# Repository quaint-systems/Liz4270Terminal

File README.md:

# Liz4270Terminal

Liz4270 is an open-source IBM 3270 CUT terminal. Its RP2350 firmware presents an IBM 3483-V to a controller over coax, drives DVI video over HDMI, and accepts a USB keyboard.

## What you need

- A Liz4270 Rev A board. The assembly order excludes the Murata 78602/8JC coax transformer (T1). Source it before ordering and fit it by hand. [Board design and bring-up](hardware/board/README.md) · [Ordering guide](hardware/board/jlc/README.md)
- A 3270 controller with a CUT coax port and a 93 Ω RG-62 cable with BNC connectors. The firmware was bench-tested on prototype hardware with oec and a Liz 4174 controller. Rev A and physical IBM 3174 bench results are still undocumented here. [oec](https://github.com/hanshuebner/oec-tcp) · [Liz 4174](https://github.com/quaint-systems/coax-tcp/tree/liz4174-v1/interface3)
- An HDMI monitor that accepts 640 × 480 at 60 Hz, a USB keyboard, and a 5 V USB-C power source. [USB keyboard map](docs/keymaps/us104.md)
- Firmware and the User’s Guide. The guide covers setup and updating over USB. [Downloads](https://github.com/quaint-systems/Liz4270Terminal/releases) · [Guide source](docs/manual/manual.typ)

For a printed enclosure, see the [printable parts and assembly instructions](hardware/case/README.md).

## Build the firmware

Install Git, CMake 3.25 or newer, Ninja, Arm GNU Toolchain 15.3.Rel1 (`arm-none-eabi`), and picotool 2.3.1. Use a Git checkout to fetch the firmware submodules.

```sh
git clone https://github.com/quaint-systems/Liz4270Terminal.git
cd Liz4270Terminal
git submodule update --init firmware/pico-sdk firmware/Pico-PIO-USB
git -C firmware/pico-sdk submodule update --init lib/tinyusb
cd firmware
cmake --preset liz4270
cmake --build --preset liz4270
```

The firmware image is `firmware/build/liz4270/liz4270.uf2`. Put the board into BOOTSEL mode and copy this file to the RP2350 USB drive. See [versioning](docs/versions.md) for how builds are identified.

## Build the user guide

Install Typst 0.15.1, Python 3.11 or newer, and a host C compiler. The manual build uses Pillow and oec to check the keyboard descriptions. Run these commands from the repository root.

```sh
git clone https://github.com/hanshuebner/oec-tcp.git ../oec-tcp
git -C ../oec-tcp checkout 3c5e812f6d2c0321e6c443dd4ed9590b7611c58a
python3 -m venv ../liz4270-docs-venv
. ../liz4270-docs-venv/bin/activate
python -m pip install -r ../oec-tcp/requirements.txt -r tools/sim/requirements.txt
PYTHONPATH=../oec-tcp python tools/manual/build.py
```

Draft PDFs for US Letter and A4 are written to `build/manual/`.

## Run the tests

See the [simulator test setup](tools/sim/README.md). To run the user guide tests as well, use the manual build environment above and run `PYTHONPATH=../oec-tcp python -m unittest discover -s tools/manual` from the repository root.

## License

- Firmware and software are licensed under [ISC](LICENSE).
- Hardware design files are licensed under [CERN-OHL-P v2](hardware/LICENSE).
- The user manual is licensed under [CC BY 4.0](docs/manual/LICENSE).
- Third-party licenses and credits are listed in [NOTICE](NOTICE).

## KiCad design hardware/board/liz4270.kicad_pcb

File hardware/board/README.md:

# Liz4270 board, revision A

The revision A board combines an RP2350B, a 3270 coax interface, DVI output, USB keyboard host, and audio.

## The schematic is generated

`liz4270.kicad_sch` and its six sheets are written by `tools/board/build_schematic.py` from `tools/board/sheet_*.py`.
**Don't edit them in KiCad**: change the sheet modules and rebuild, or the next build overwrites the edit, and
`tools/board/test_board.py` fails while the two disagree.

A sheet lists each part with its nets, as labels on short stubs, or draws a circuit with wires: `Sheet.drawing()` in
`tools/board/schematic.py`. Every sheet is drawn, with its decoupling banks and the like still listed.

```bash
python3 tools/board/build_schematic.py
python3 -m unittest discover -s tools/board -p 'test_*.py'
```

The tests need KiCad 10 (`kicad-cli`). They check the netlist against the board pin map and topology, every
supply pin's rail, which parts are fitted, every part's LCSC number, and ERC.

## Sheets

| Sheet | What |
| --- | --- |
| MCU | RP2350B on the Fruit Jam's pin map; core regulator and crystal as Raspberry Pi's minimal design; flash; BOOTSEL and RESET; SWD; the bench header; drawn as a circuit, with BOOTSEL, SWD and the bench header beside it and the decoupling listed |
| Coax | the Liz 4174's port 1 (interface3 port 0), with TX_ACTIVE's pull-down and the unused channels held; drawn as a circuit |
| Video | HSTX DVI through 220 R; TPD13S523; DDC level shifter; hot-plug to GPIO7; drawn as a circuit, with the TPD13S523's clamps by label |
| USB host | AP2171W port switch; CH334F hub; stacked dual USB-A with ESD on each port; drawn as a circuit |
| Audio | TLV320DAC3100 and its 1.8 V; speaker connector; drawn as circuits, the decoupling listed |
| Power | USB-C input and protection, 3.3 V LDO and power LED, drawn as a circuit; test points and mounting holes, bare copper that JLC's order leaves out |

## The board is generated

`liz4270.kicad_pcb`, `liz4270.kicad_pro` and `liz4270.kicad_dru` are written by `tools/board/build_board.py`, from
the schematic's netlist and `tools/board/layout.py`. **Don't save the board from KiCad**: a review that does is undone
with `git checkout hardware/board/`, and `test_layout.py` fails while the files and the generator disagree.
`build_board.py --check` builds it in a scratch directory and lists what differs.

- **The layout is Python.** `layout.py` draws the outline and runs one `layout_<block>.py` per block, in order: edge,
  MCU (with `regulator.py`, Raspberry Pi's minimal design moved onto U1), coax, video, USB host, power, audio, then
  the escapes and the planes. Each block places its parts and may add scripted copper, by pad name (`'U1.63'`) or by
  point. `pcb_build.py` runs it in KiCad's own Python (3.9, the one with `pcbnew`).
- **Coordinates** are board millimetres from the outline's top-left corner, x to the right, y down; angles turn
  counter-clockwise, as KiCad shows them. The board sits at (20, 20) on KiCad's page with the grid and drill origins
  there, so the GUI reads the same numbers as the code.
- **The floorplan,** 100 x 80 mm, four layers (In1 ground, In2 +3V3). The connector edge is the bottom, y = 80: the
  BNC (J3, x 10), USB-C (J6, x 30), the USB-A pair (J5, x 49.5), HDMI (J4, x 71), BOOTSEL behind its pinhole (SW1,
  x 85) and RESET in the corner (SW2, x 94.6).

  | Block | Where |
  | --- | --- |
  | MCU | U1 at (42, 32), turned 180°: its coax pins face left, HSTX right, the regulator, QSPI and USB down; Y1, J1 (SWD) and J2 (bench header) above it |
  | Coax | U3 and U4 at x 10–21, y 38; T1 at (10, 57); the line side, x 0–19.5 below y 59, with the BNC, inside a 1.5 mm band no copper crosses on any layer |
  | Video | R20–R27 right of U1; U6 at (75.5, 61) behind HDMI |
  | USB host | U8 at (57.75, 50), Y2, U7, and U9/U10 at the USB-A pair |
  | Power | U12 at (29, 52), U11, F1, D4 and FB1 behind USB-C |
  | Audio | U14 at (78, 16), U13 and J7 (speaker) in the top right |

- **Routing** is partly scripted and partly Freerouting's. The blocks script what must not move: TMDS and USB pairs
  matched in length, the crystals, the regulator, the coax drive and the line side, the power spines.
  `tools/board/autoroute.py` routes the rest with Freerouting 2.4.1 (a few minutes) and keeps its session beside the
  board: `liz4270.ses`, with `liz4270.route.json`, a fingerprint of everything the routes were made from (layout,
  net classes, rules, footprints). `build_board.py` takes the session in only while the fingerprint matches;
  otherwise it builds the board unrouted and says so, and `TestRouted.test_the_session_is_current` fails. A rerun
  reshuffles all of Freerouting's copper and can leave a pin or two unconnected, which an escape in
  `layout_escapes.py` fixes; check DRC after each.
- **The zones are saved unfilled.** KiCad's filler doesn't give the same polygons from one run to the next, so a
  filled board couldn't be checked byte for byte. DRC, the plots and the tests fill them; in the GUI, press B.

The other generators, each with `--check` where it writes committed files:

- `render_board.py`: PNG renders of layers, crops, or the 3D view, for looking at a layout.
- `make_models.py`: plain-body STEP models, through FreeCAD, for the footprints KiCad 10.0.6 has no model for.
- `make_exports.py`: `export/`, the outline DXF, the holes, fronts, inside parts and labels as JSON, and the same
  as an OpenSCAD include for the case (`hardware/case/`, #134); and its STEP and STL (made, not committed).
- `make_jlc.py`: `jlc/`, the Gerbers, BOM and placement file for JLC; `jlc/README.md` gives the order's options.

## Not fitted on revision A

R3 (QSPI_SS pull-up, only for another flash), U5 and C26 (coax ESD, bring-up step 7 decides), C61 (100 n on RUN, for a
board that resets by itself), J2 (bench header). None of them is on JLC's order, and neither is T1, fitted by hand
on spin 1 (`jlc/README.md`).

## Bring-up notes

- About 50 µF sits on +5V with no inrush limit, as on the Fruit Jam.
- Scope +5V while plugging in a short USB-C cable. SPKVDD and the TPD13S523 are rated only to 6.0 V, and the SMAJ5.0A
  starts clamping at 6.4 V. If +5V overshoots, add damped bulk.
- When GPIO11 goes high, the AP2171 charges about 210 µF at its current limit for about 1 ms. Check that the console
  doesn't drop.
- T1 is fitted by hand: a J-lead on a 2.54 mm pitch, line pins (1, 6) toward the BNC.

## License

CERN-OHL-P v2 (`hardware/LICENSE`, the text from
https://gitlab.com/ohwr/project/cernohl/-/wikis/uploads/3eff4154d05e7a0459f3ddbf0674cae4/cern_ohl_p_v2.txt,
where https://ohwr.org/cern_ohl_p_v2.txt redirects). The coax front end is interface3's (ISC, Hans Hübner), and the
core regulator follows Raspberry Pi's RP2350 minimal design (MIT); `NOTICE` lists both.

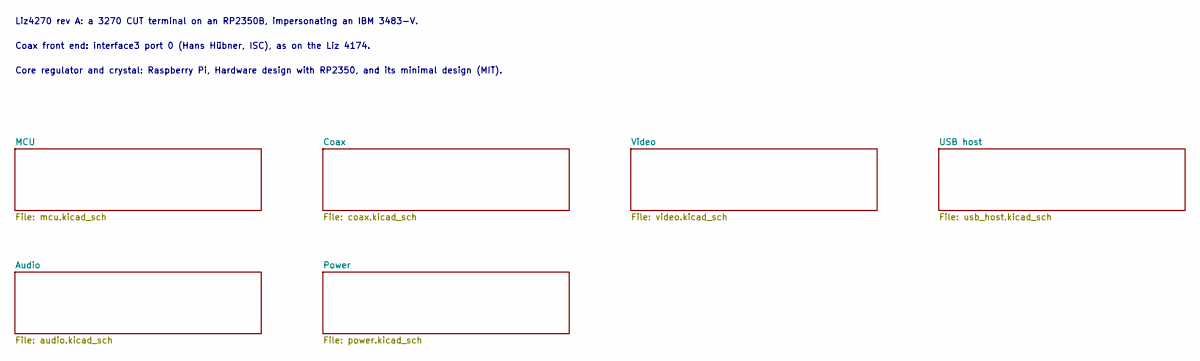
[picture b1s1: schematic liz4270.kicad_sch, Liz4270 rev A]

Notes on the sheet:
Liz4270 rev A: a 3270 CUT terminal on an RP2350B, impersonating an IBM 3483-V.
Coax front end: interface3 port 0 (Hans Hübner, ISC), as on the Liz 4174.
Core regulator and crystal: Raspberry Pi, Hardware design with RP2350, and its minimal design (MIT).

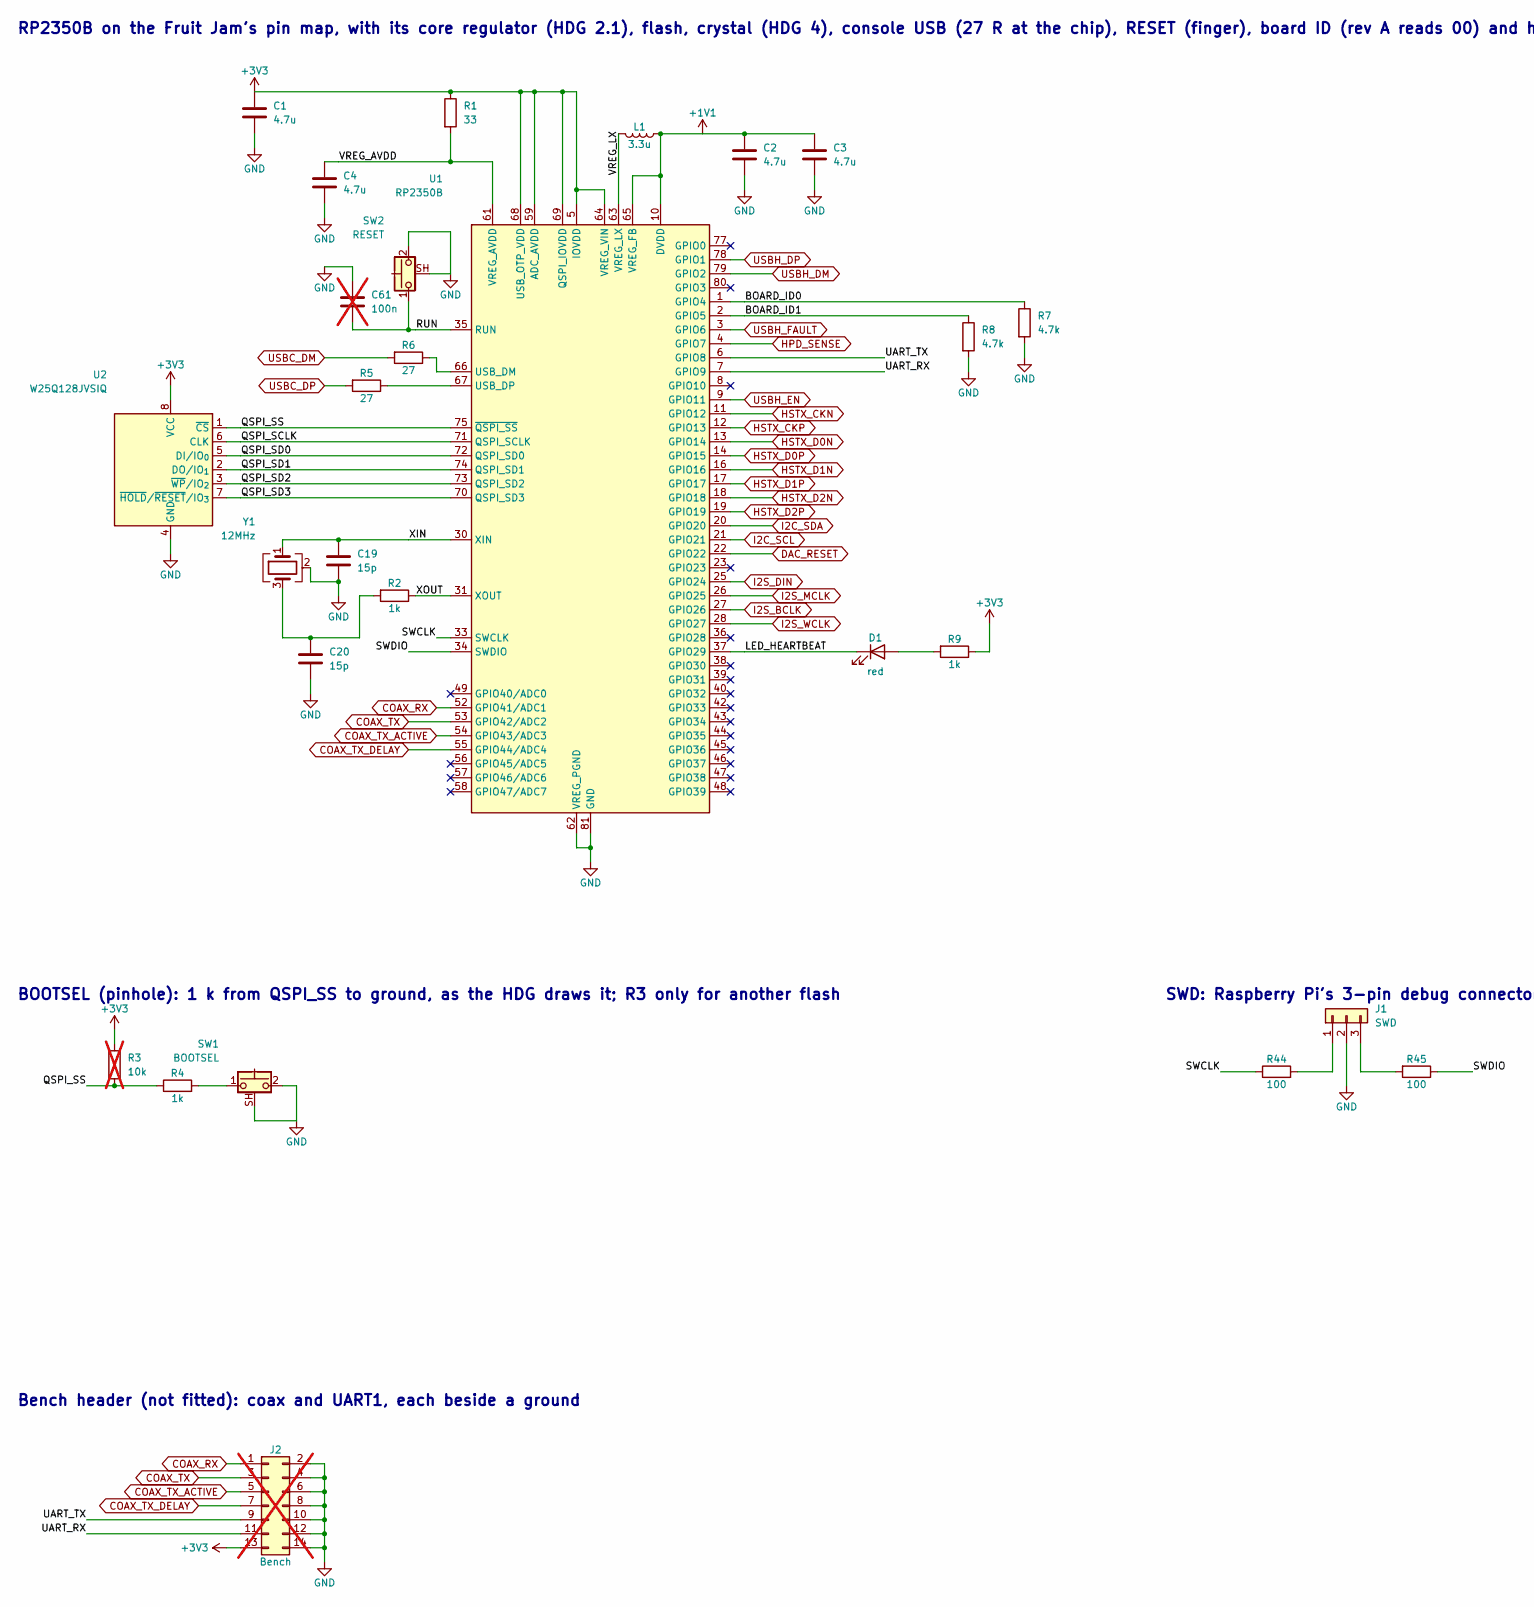
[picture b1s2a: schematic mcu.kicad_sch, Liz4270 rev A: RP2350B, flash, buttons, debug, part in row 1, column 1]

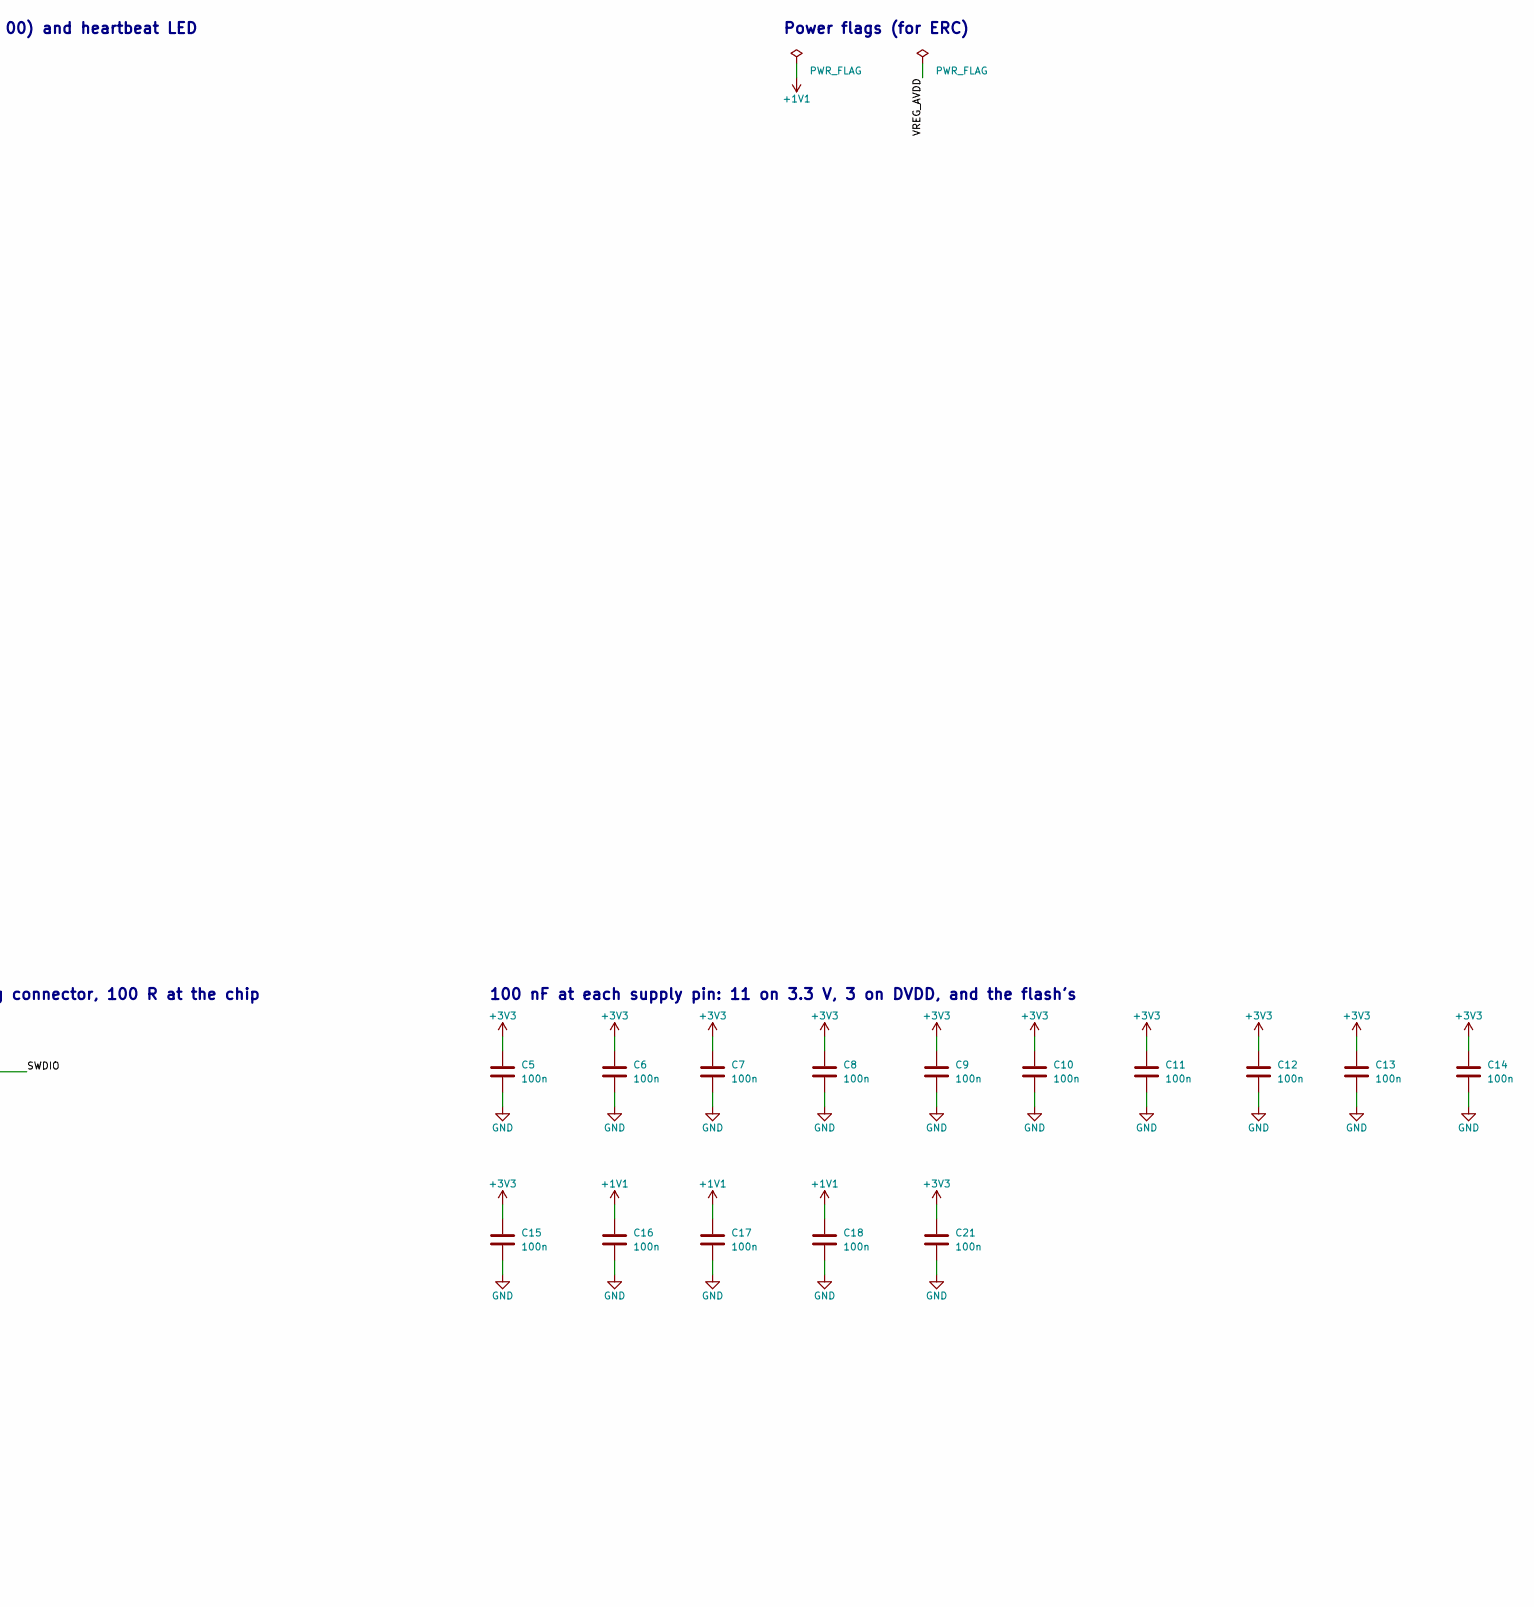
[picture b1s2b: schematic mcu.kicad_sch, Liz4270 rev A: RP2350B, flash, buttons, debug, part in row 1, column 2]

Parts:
C1, C2: 4.7u; RPi_C_1005_Wide; LCSC C23733
C3, C4: 4.7u; C_0402_1005Metric; LCSC C23733
C5, C6, C7, C8, C9, C10, C11, C12, C13, C14, C15, C16, C17, C18, C21: 100n; C_0603_1608Metric; LCSC C14663
C19, C20: 15p; C_0603_1608Metric; LCSC C1644
C61: 100n; C_0603_1608Metric; LCSC C14663; not fitted
D1: red; LED_0603_1608Metric; MPN KT-0603R; LCSC C2286
J1: SWD; JST_SH_SM03B-SRSS-TB_1x03-1MP_P1.00mm_Horizontal; MPN 1.0-3PWT; LCSC C2763613
J2: Bench; PinHeader_2x07_P2.54mm_Vertical; MPN 2.54-2*7P; LCSC C71397; not fitted
L1: 3.3u; Abracon_AOTA-B201610S3R3-101-T; MPN AOTA-B201610S3R3-101-T; LCSC C42411119
R1: 33; R_0402_1005Metric; LCSC C25105
R2, R4, R9: 1k; R_0603_1608Metric; LCSC C21190
R3: 10k; R_0603_1608Metric; LCSC C25804; not fitted
R5, R6: 27; R_0603_1608Metric; LCSC C25190
R7, R8: 4.7k; R_0603_1608Metric; LCSC C23162
R44, R45: 100; R_0603_1608Metric; LCSC C22775
SW1: BOOTSEL; SW_CK_PTS645V_Angled; MPN PTS645VK392LFS; LCSC C285519
SW2: RESET; SW_CK_PTS645V_Angled; MPN PTS645VK392LFS; LCSC C285519
U1: RP2350B; QFN-80-1EP_10x10mm_P0.4mm_EP3.4x3.4mm_ThermalVias; MPN RP2350B; LCSC C42415655
U2: W25Q128JVSIQ; SOIC-8_5.3x5.3mm_P1.27mm; MPN W25Q128JVSIQ; LCSC C97521
Y1: 12MHz; Crystal_SMD_3225-4Pin_3.2x2.5mm; MPN ABM8-272-T3; LCSC C20625731

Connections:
+1V1: C2.1, C3.1, C16.1, C17.1, C18.1, L1.1, U1.10 (DVDD), U1.32 (DVDD), U1.51 (DVDD), U1.65 (VREG_FB); also elsewhere on the board
+3V3: C1.1, C5.1, C6.1, C7.1, C8.1, C9.1, C10.1, C11.1, C12.1, C13.1, C14.1, C15.1, C21.1, J2.13, R1.1, R3.1, R9.1, U1.5 (IOVDD), U1.15 (IOVDD), U1.24 (IOVDD), U1.29 (IOVDD), U1.41 (IOVDD), U1.50 (IOVDD), U1.59 (ADC_AVDD), U1.60 (IOVDD), U1.64 (VREG_VIN), U1.68 (USB_OTP_VDD), U1.69 (QSPI_IOVDD), U1.76 (IOVDD), U2.8 (VCC); also elsewhere on the board
/MCU/BOARD_ID0: R7.1, U1.1 (GPIO4)
/MCU/BOARD_ID1: R8.1, U1.2 (GPIO5)
/MCU/LED_HEARTBEAT: D1.1 (K), U1.37 (GPIO29)
/MCU/QSPI_SCLK: U1.71 (QSPI_SCLK), U2.6 (CLK)
/MCU/QSPI_SD0: U1.72 (QSPI_SD0), U2.5 (DI/IO_{0})
/MCU/QSPI_SD1: U1.74 (QSPI_SD1), U2.2 (DO/IO_{1})
/MCU/QSPI_SD2: U1.73 (QSPI_SD2), U2.3 (~WP/IO_{2})
/MCU/QSPI_SD3: U1.70 (QSPI_SD3), U2.7 (~HOLD/~RESET/IO_{3})
/MCU/QSPI_SS: R3.2, R4.1, U1.75 (~QSPI_SS), U2.1 (~CS)
/MCU/RUN: C61.1, SW2.1, U1.35 (RUN)
/MCU/SWCLK: R44.1, U1.33 (SWCLK)
/MCU/SWDIO: R45.1, U1.34 (SWDIO)
/MCU/UART_RX: J2.11, U1.7 (GPIO9)
/MCU/UART_TX: J2.9, U1.6 (GPIO8)
/MCU/VREG_AVDD: C4.1, R1.2, U1.61 (VREG_AVDD)
/MCU/VREG_LX: L1.2, U1.63 (VREG_LX)
/MCU/XIN: C19.1, U1.30 (XIN), Y1.1
/MCU/XOUT: R2.1, U1.31 (XOUT)
COAX_RX: J2.1, U1.52 (GPIO41/ADC1); also elsewhere on the board
COAX_TX: J2.3, U1.53 (GPIO42/ADC2); also elsewhere on the board
COAX_TX_ACTIVE: J2.5, U1.54 (GPIO43/ADC3); also elsewhere on the board
COAX_TX_DELAY: J2.7, U1.55 (GPIO44/ADC4); also elsewhere on the board
DAC_RESET: U1.22 (GPIO22); also elsewhere on the board
GND: C1.2, C2.2, C3.2, C4.2, C5.2, C6.2, C7.2, C8.2, C9.2, C10.2, C11.2, C12.2, C13.2, C14.2, C15.2, C16.2, C17.2, C18.2, C19.2, C20.2, C21.2, C61.2, J1.2, J2.2, J2.4, J2.6, J2.8, J2.10, J2.12, J2.14, R7.2, R8.2, SW1.2, SW1.SH (B), SW2.2, SW2.SH (B), U1.62 (VREG_PGND), U1.81 (GND), U2.4 (GND), Y1.2 (G), Y1.4 (G); also elsewhere on the board
HPD_SENSE: U1.4 (GPIO7); also elsewhere on the board
HSTX_CKN: U1.11 (GPIO12); also elsewhere on the board
HSTX_CKP: U1.12 (GPIO13); also elsewhere on the board
HSTX_D0N: U1.13 (GPIO14); also elsewhere on the board
HSTX_D0P: U1.14 (GPIO15); also elsewhere on the board
HSTX_D1N: U1.16 (GPIO16); also elsewhere on the board
HSTX_D1P: U1.17 (GPIO17); also elsewhere on the board
HSTX_D2N: U1.18 (GPIO18); also elsewhere on the board
HSTX_D2P: U1.19 (GPIO19); also elsewhere on the board
I2C_SCL: U1.21 (GPIO21); also elsewhere on the board
I2C_SDA: U1.20 (GPIO20); also elsewhere on the board
I2S_BCLK: U1.27 (GPIO26); also elsewhere on the board
I2S_DIN: U1.25 (GPIO24); also elsewhere on the board
I2S_MCLK: U1.26 (GPIO25); also elsewhere on the board
I2S_WCLK: U1.28 (GPIO27); also elsewhere on the board
unnamed: C20.1, R2.2, Y1.3
unnamed: D1.2 (A), R9.2
unnamed: J1.1, R44.2
unnamed: J1.3, R45.2
unnamed: R4.2, SW1.1
unnamed: R6.1, U1.66 (USB_DM)
unnamed: R5.1, U1.67 (USB_DP)
USBC_DM: R6.2; also elsewhere on the board
USBC_DP: R5.2; also elsewhere on the board
USBH_DM: U1.79 (GPIO2); also elsewhere on the board
USBH_DP: U1.78 (GPIO1); also elsewhere on the board
USBH_EN: U1.9 (GPIO11); also elsewhere on the board
USBH_FAULT: U1.3 (GPIO6); also elsewhere on the board

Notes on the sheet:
RP2350B on the Fruit Jam's pin map, with its core regulator (HDG 2.1), flash, crystal (HDG 4), console USB (27 R at the chip), RESET (finger), board ID (rev A reads 00) and heartbeat LED
Power flags (for ERC)
BOOTSEL (pinhole): 1 k from QSPI_SS to ground, as the HDG draws it; R3 only for another flash
SWD: Raspberry Pi's 3-pin debug connector, 100 R at the chip
100 nF at each supply pin: 11 on 3.3 V, 3 on DVDD, and the flash's
Bench header (not fitted): coax and UART1, each beside a ground

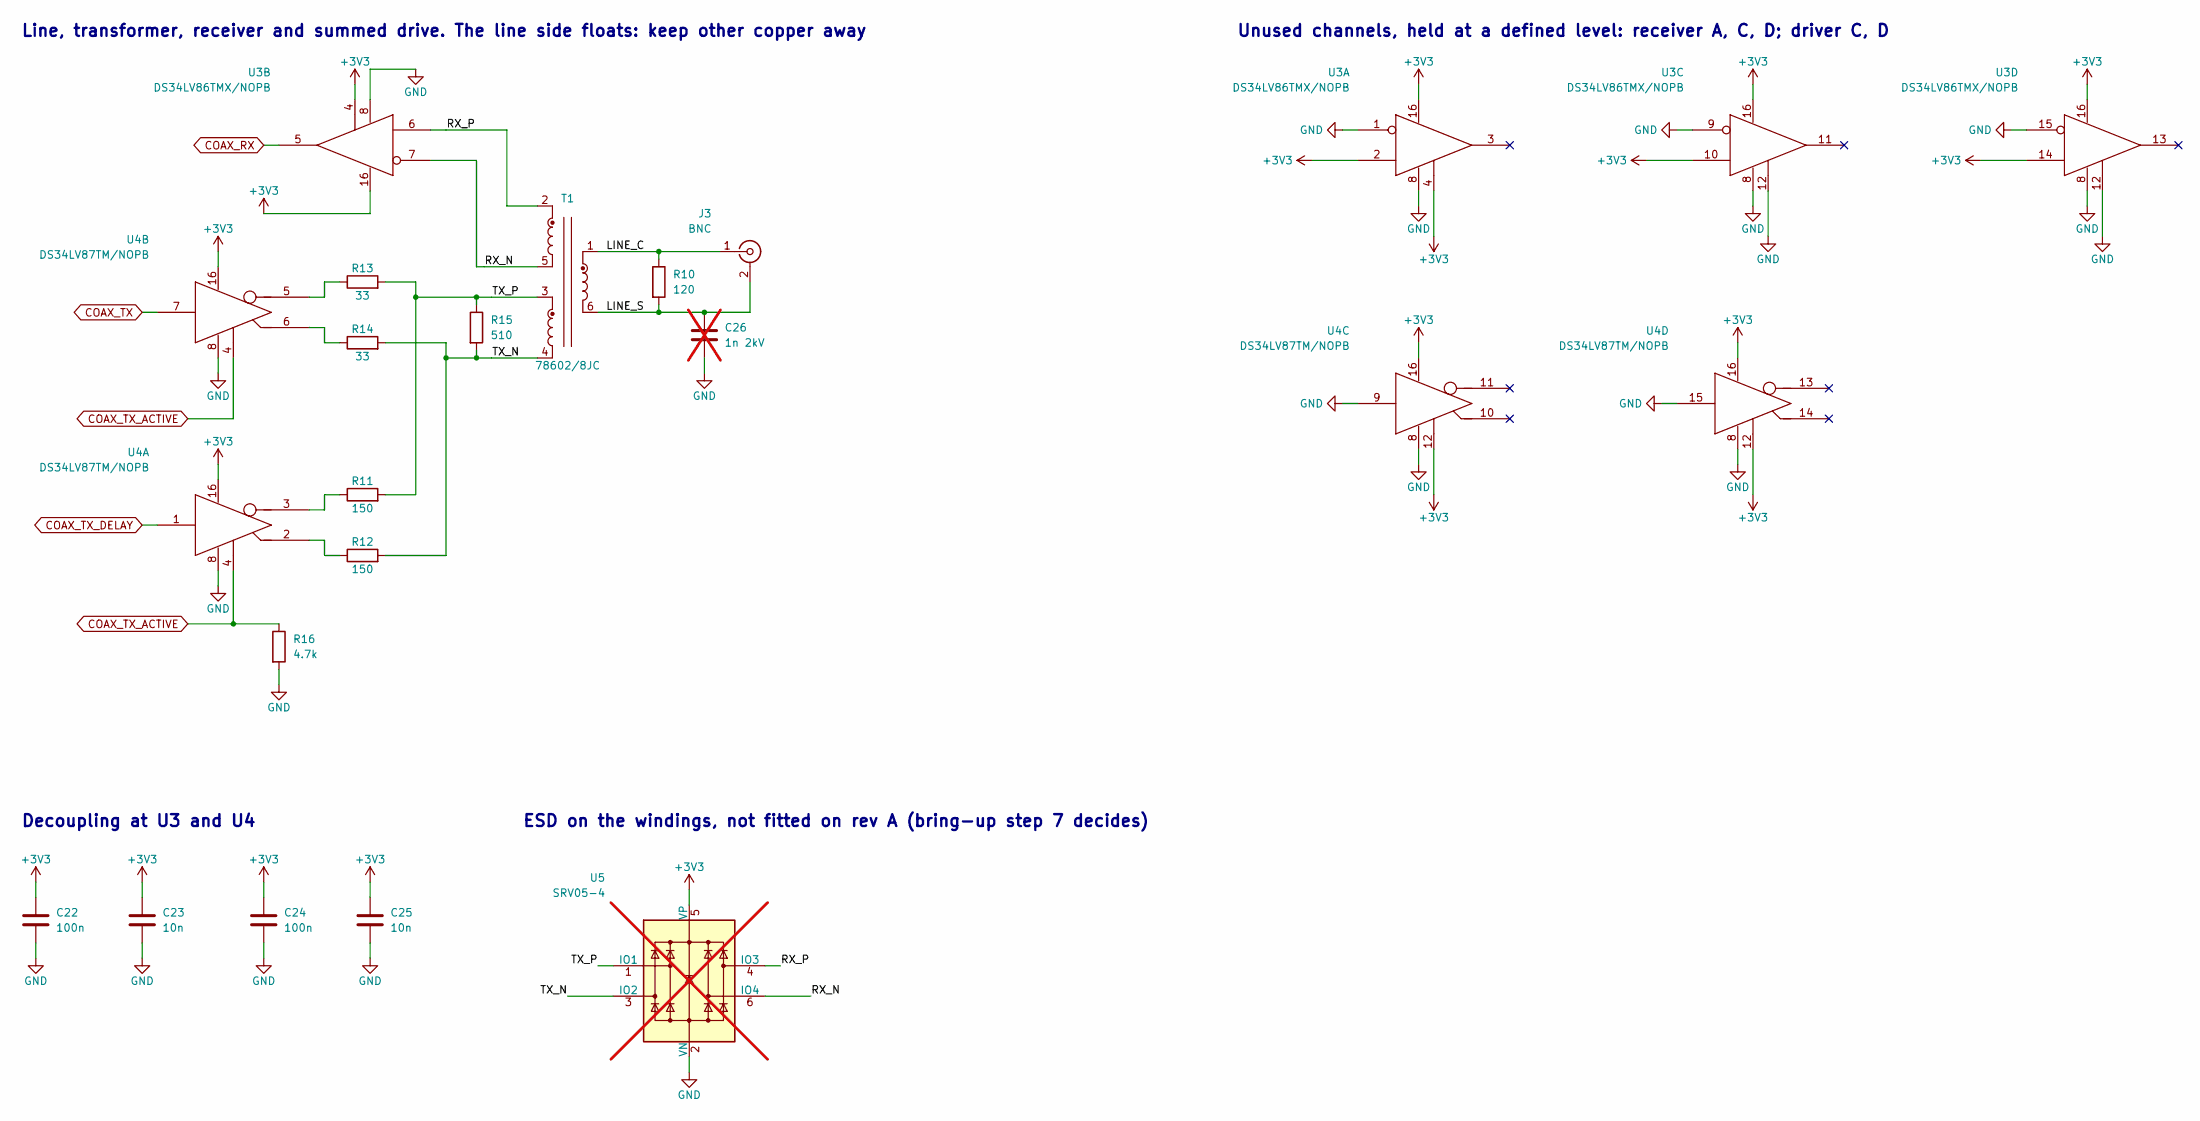
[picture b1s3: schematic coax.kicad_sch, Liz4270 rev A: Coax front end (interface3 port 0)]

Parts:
C22, C24: 100n; C_0603_1608Metric; LCSC C14663
C23, C25: 10n; C_0603_1608Metric; LCSC C57112
C26: 1n 2kV; C_1206_3216Metric; LCSC C9196; not fitted
J3: BNC; BNC_Amphenol_B6252HB-NPP3G-50_Horizontal; MPN B6252HB-NPP3G-50; LCSC C22457552
R10: 120; R_0603_1608Metric; LCSC C22787
R11, R12: 150; R_0603_1608Metric; LCSC C22808
R13, R14: 33; R_0603_1608Metric; LCSC C23140
R15: 510; R_0603_1608Metric; LCSC C23193
R16: 4.7k; R_0603_1608Metric; LCSC C23162
T1: 78602/8JC; Murata_786J; MPN 78602/8JC; LCSC C7040198
U3: DS34LV86TMX/NOPB; SOIC-16_3.9x9.9mm_P1.27mm; MPN DS34LV86TMX/NOPB; LCSC C140249
U4: DS34LV87TM/NOPB; SOIC-16_3.9x9.9mm_P1.27mm; MPN DS34LV87TM/NOPB; LCSC C1543778
U5: SRV05-4; SOT-23-6; MPN SRV05-4.TCT; LCSC C13612; not fitted

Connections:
+3V3: C22.1, C23.1, C24.1, C25.1, U3.2 (E+), U3.4 (ENABLE), U3.10 (E+), U3.14 (E+), U3.16 (VCC), U4.12 (ENABLE), U4.16 (VCC), U5.5 (VP); also elsewhere on the board
/Coax/LINE_C: J3.1 (In), R10.1, T1.1
/Coax/LINE_S: C26.1, J3.2 (Ext), R10.2, T1.6
/Coax/RX_N: T1.5, U3.7 (E-), U5.6 (IO4)
/Coax/RX_P: T1.2, U3.6 (E+), U5.4 (IO3)
/Coax/TX_N: R12.2, R14.2, R15.2, T1.4, U5.3 (IO2)
/Coax/TX_P: R11.2, R13.2, R15.1, T1.3, U5.1 (IO1)
COAX_RX: U3.5 (OUT); also elsewhere on the board
COAX_TX: U4.7 (INPUT); also elsewhere on the board
COAX_TX_ACTIVE: R16.1, U4.4 (ENABLE); also elsewhere on the board
COAX_TX_DELAY: U4.1 (INPUT); also elsewhere on the board
GND: C22.2, C23.2, C24.2, C25.2, C26.2, R16.2, U3.1 (E-), U3.8 (GND), U3.9 (E-), U3.12 (ENABLE), U3.15 (E-), U4.8 (GND), U4.9 (INPUT), U4.15 (INPUT), U5.2 (VN); also elsewhere on the board
unnamed: R12.1, U4.2 (OUT+)
unnamed: R11.1, U4.3 (OUT-)
unnamed: R14.1, U4.6 (OUT+)
unnamed: R13.1, U4.5 (OUT-)

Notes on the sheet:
Line, transformer, receiver and summed drive. The line side floats: keep other copper away
Unused channels, held at a defined level: receiver A, C, D; driver C, D
Decoupling at U3 and U4
ESD on the windings, not fitted on rev A (bring-up step 7 decides)

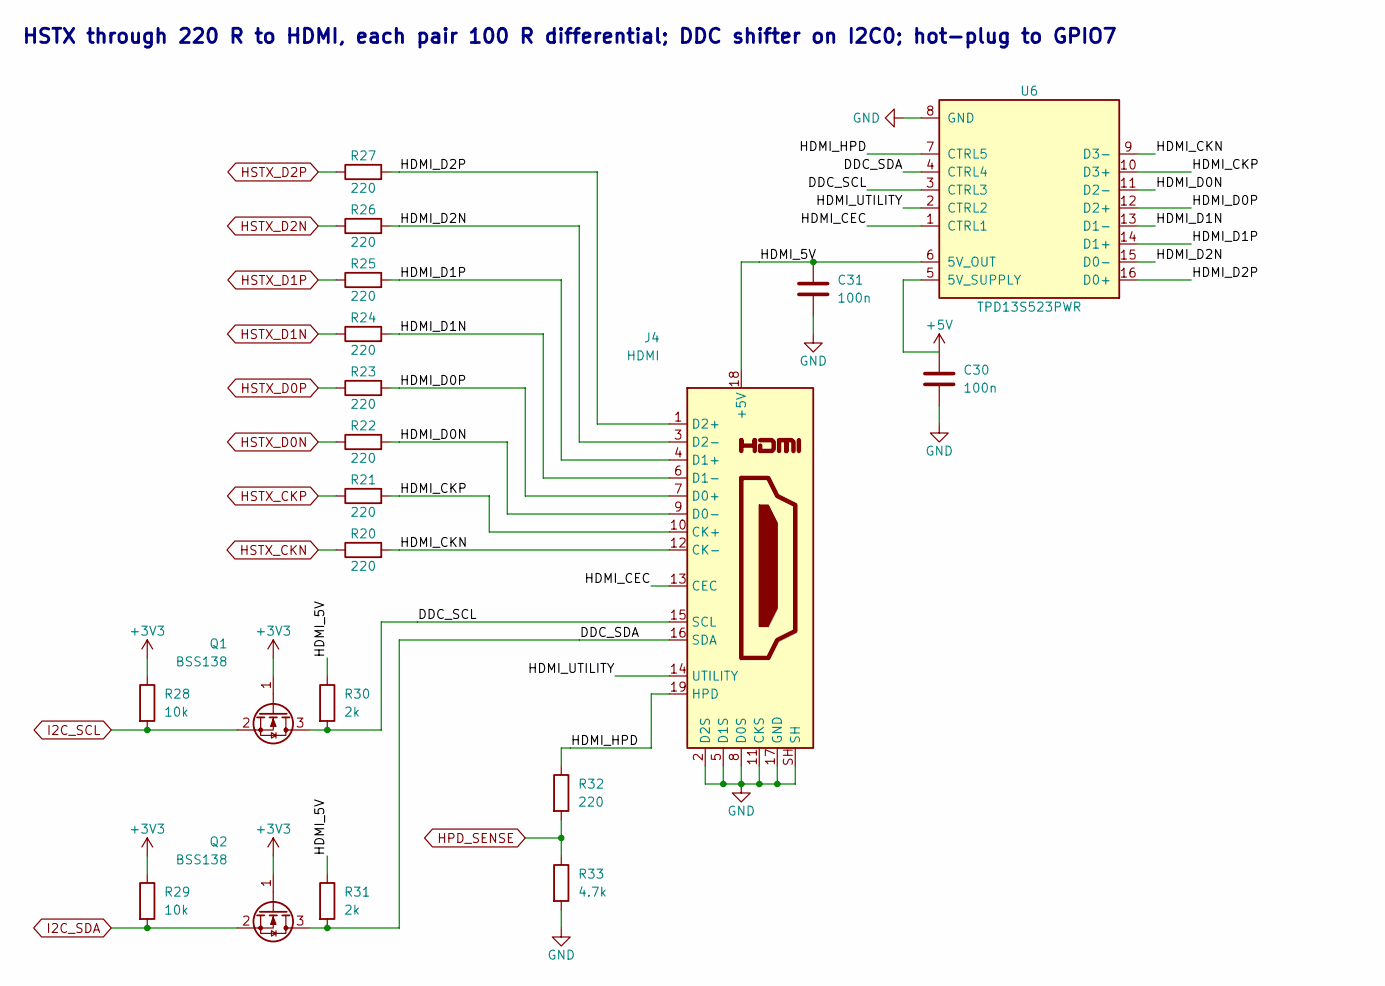
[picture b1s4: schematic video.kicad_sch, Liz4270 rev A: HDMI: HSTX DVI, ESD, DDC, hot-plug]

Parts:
C30, C31: 100n; C_0603_1608Metric; LCSC C14663
J4: HDMI; HDMI_A_Molex_208658-1001_Horizontal; MPN 2086581001; LCSC C916313
Q1, Q2: BSS138; SOT-23; MPN BSS138LT1G; LCSC C82045
R20, R21, R22, R23, R24, R25, R26, R27, R32: 220; R_0603_1608Metric; LCSC C22962
R28, R29: 10k; R_0603_1608Metric; LCSC C25804
R30, R31: 2k; R_0603_1608Metric; LCSC C22975
R33: 4.7k; R_0603_1608Metric; LCSC C23162
U6: TPD13S523PWR; TSSOP-16_4.4x5mm_P0.65mm; MPN TPD13S523PWR; LCSC C2865622

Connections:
+3V3: Q1.1 (G), Q2.1 (G), R28.1, R29.1; also elsewhere on the board
+5V: C30.1, U6.5 (5V_SUPPLY); also elsewhere on the board
/Video/DDC_SCL: J4.15 (SCL), Q1.3 (D), R30.2, U6.3 (CTRL3)
/Video/DDC_SDA: J4.16 (SDA), Q2.3 (D), R31.2, U6.4 (CTRL4)
/Video/HDMI_5V: C31.1, J4.18 (+5V), R30.1, R31.1, U6.6 (5V_OUT)
/Video/HDMI_CEC: J4.13 (CEC), U6.1 (CTRL1)
/Video/HDMI_CKN: J4.12 (CK-), R20.2, U6.9 (D3-)
/Video/HDMI_CKP: J4.10 (CK+), R21.2, U6.10 (D3+)
/Video/HDMI_D0N: J4.9 (D0-), R22.2, U6.11 (D2-)
/Video/HDMI_D0P: J4.7 (D0+), R23.2, U6.12 (D2+)
/Video/HDMI_D1N: J4.6 (D1-), R24.2, U6.13 (D1-)
/Video/HDMI_D1P: J4.4 (D1+), R25.2, U6.14 (D1+)
/Video/HDMI_D2N: J4.3 (D2-), R26.2, U6.15 (D0-)
/Video/HDMI_D2P: J4.1 (D2+), R27.2, U6.16 (D0+)
/Video/HDMI_HPD: J4.19 (HPD), R32.1, U6.7 (CTRL5)
/Video/HDMI_UTILITY: J4.14 (UTILITY), U6.2 (CTRL2)
GND: C30.2, C31.2, J4.2 (D2S), J4.5 (D1S), J4.8 (D0S), J4.11 (CKS), J4.17 (GND), J4.SH, R33.2, U6.8 (GND); also elsewhere on the board
HPD_SENSE: R32.2, R33.1; also elsewhere on the board
HSTX_CKN: R20.1; also elsewhere on the board
HSTX_CKP: R21.1; also elsewhere on the board
HSTX_D0N: R22.1; also elsewhere on the board
HSTX_D0P: R23.1; also elsewhere on the board
HSTX_D1N: R24.1; also elsewhere on the board
HSTX_D1P: R25.1; also elsewhere on the board
HSTX_D2N: R26.1; also elsewhere on the board
HSTX_D2P: R27.1; also elsewhere on the board
I2C_SCL: Q1.2 (S), R28.2; also elsewhere on the board
I2C_SDA: Q2.2 (S), R29.2; also elsewhere on the board

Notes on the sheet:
HSTX through 220 R to HDMI, each pair 100 R differential; DDC shifter on I2C0; hot-plug to GPIO7

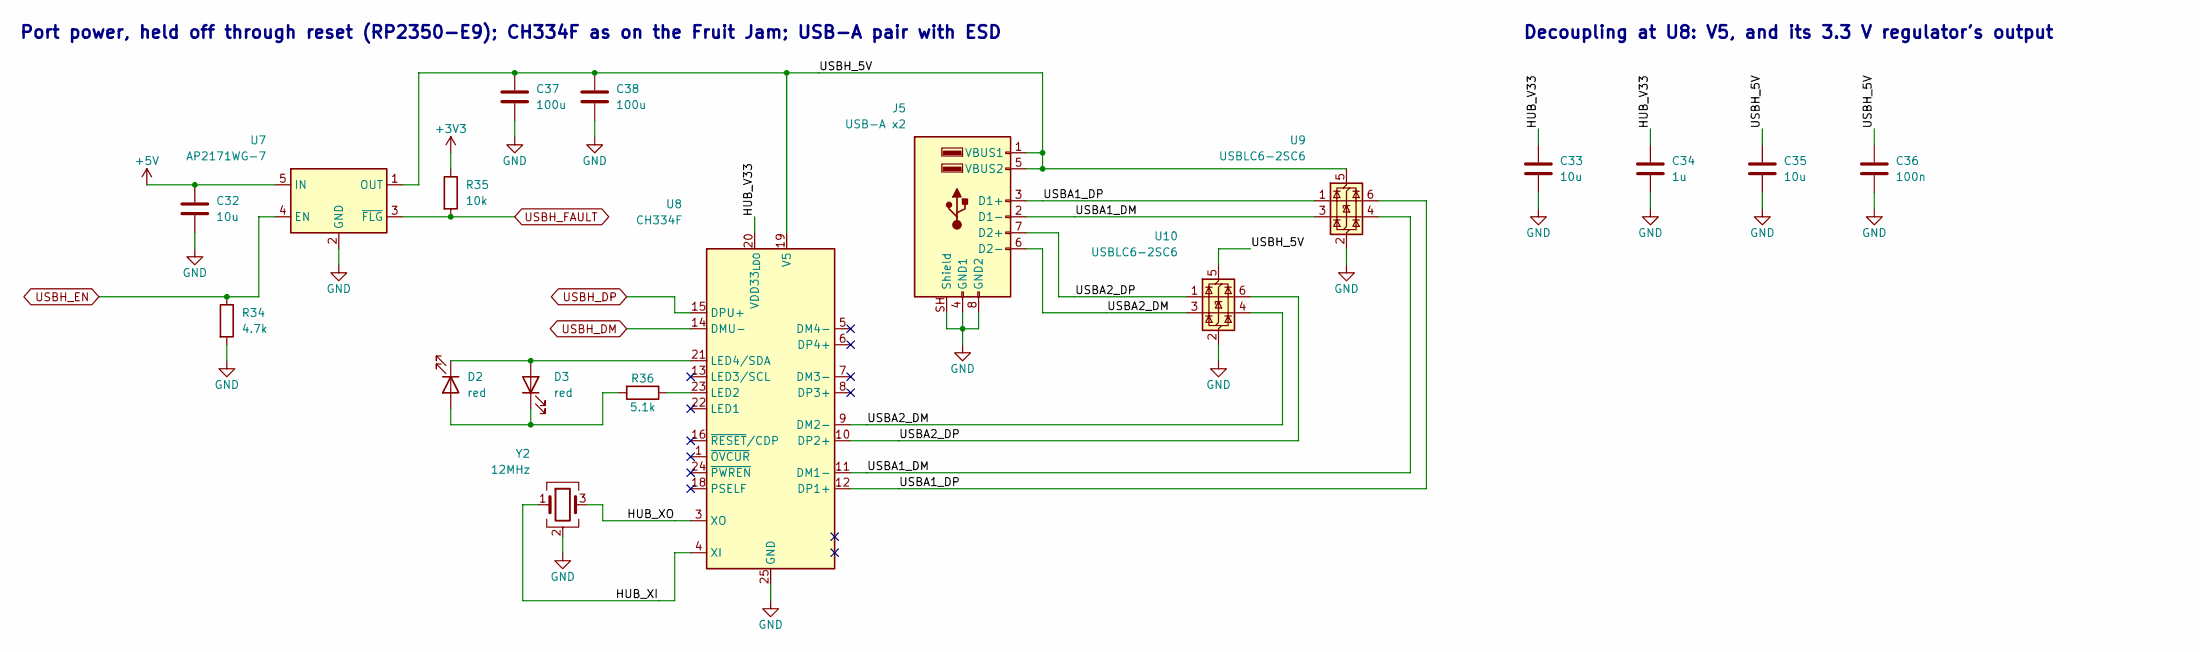
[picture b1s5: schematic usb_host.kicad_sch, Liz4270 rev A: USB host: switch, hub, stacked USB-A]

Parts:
C32, C33, C35: 10u; C_0805_2012Metric; LCSC C15850
C34: 1u; C_0603_1608Metric; LCSC C15849
C36: 100n; C_0603_1608Metric; LCSC C14663
C37, C38: 100u; C_1206_3216Metric; LCSC C15008
D2, D3: red; LED_0603_1608Metric; MPN KT-0603R; LCSC C2286
J5: USB-A x2; USB_A_Wuerth_61400826021_Horizontal_Stacked; MPN 67298-3091; LCSC C588409
R34: 4.7k; R_0603_1608Metric; LCSC C23162
R35: 10k; R_0603_1608Metric; LCSC C25804
R36: 5.1k; R_0603_1608Metric; LCSC C23186
U7: AP2171WG-7; SOT-23-5; MPN AP2171WG-7; LCSC C110466
U8: CH334F; QFN-24-1EP_4x4mm_P0.5mm_EP2.7x2.7mm_ThermalVias; MPN CH334F; LCSC C5187527
U9, U10: USBLC6-2SC6; SOT-23-6; MPN USBLC6-2SC6; LCSC C7519
Y2: 12MHz; Crystal_SMD_3225-4Pin_3.2x2.5mm; MPN ABM8-272-T3; LCSC C20625731

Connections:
+3V3: R35.1; also elsewhere on the board
+5V: C32.1, U7.5 (IN); also elsewhere on the board
/USB host/HUB_V33: C33.1, C34.1, U8.20 (VDD33_{LDO})
/USB host/HUB_XI: U8.4 (XI), Y2.1
/USB host/HUB_XO: U8.3 (XO), Y2.3
/USB host/USBA1_DM: J5.2 (D1-), U8.11 (DM1-), U9.3 (I/O2), U9.4 (I/O2)
/USB host/USBA1_DP: J5.3 (D1+), U8.12 (DP1+), U9.1 (I/O1), U9.6 (I/O1)
/USB host/USBA2_DM: J5.6 (D2-), U8.9 (DM2-), U10.3 (I/O2), U10.4 (I/O2)
/USB host/USBA2_DP: J5.7 (D2+), U8.10 (DP2+), U10.1 (I/O1), U10.6 (I/O1)
/USB host/USBH_5V: C35.1, C36.1, C37.1, C38.1, J5.1 (VBUS1), J5.5 (VBUS2), U7.1 (OUT), U8.19 (V5), U9.5 (VBUS), U10.5 (VBUS)
GND: C32.2, C33.2, C34.2, C35.2, C36.2, C37.2, C38.2, J5.4 (GND1), J5.8 (GND2), J5.SH (Shield), R34.2, U7.2 (GND), U8.25 (GND), U9.2 (GND), U10.2 (GND), Y2.2 (G), Y2.4 (G); also elsewhere on the board
unnamed: D2.2 (A), D3.1 (K), R36.2
unnamed: D2.1 (K), D3.2 (A), U8.21 (LED4/SDA)
unnamed: R36.1, U8.23 (LED2)
USBH_DM: U8.14 (DMU-); also elsewhere on the board
USBH_DP: U8.15 (DPU+); also elsewhere on the board
USBH_EN: R34.1, U7.4 (EN); also elsewhere on the board
USBH_FAULT: R35.2, U7.3 (~FLG); also elsewhere on the board

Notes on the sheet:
Port power, held off through reset (RP2350-E9); CH334F as on the Fruit Jam; USB-A pair with ESD
Decoupling at U8: V5, and its 3.3 V regulator's output

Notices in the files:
hardware/board/audio.kicad_sch:
CERN-OHL-P-2.0
hardware/board/liz4270.kicad_pcb:
© 2026 CoffeeMuse
